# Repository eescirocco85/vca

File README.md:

# vca
Voltage Controlled Amp with loudness for our Record Player

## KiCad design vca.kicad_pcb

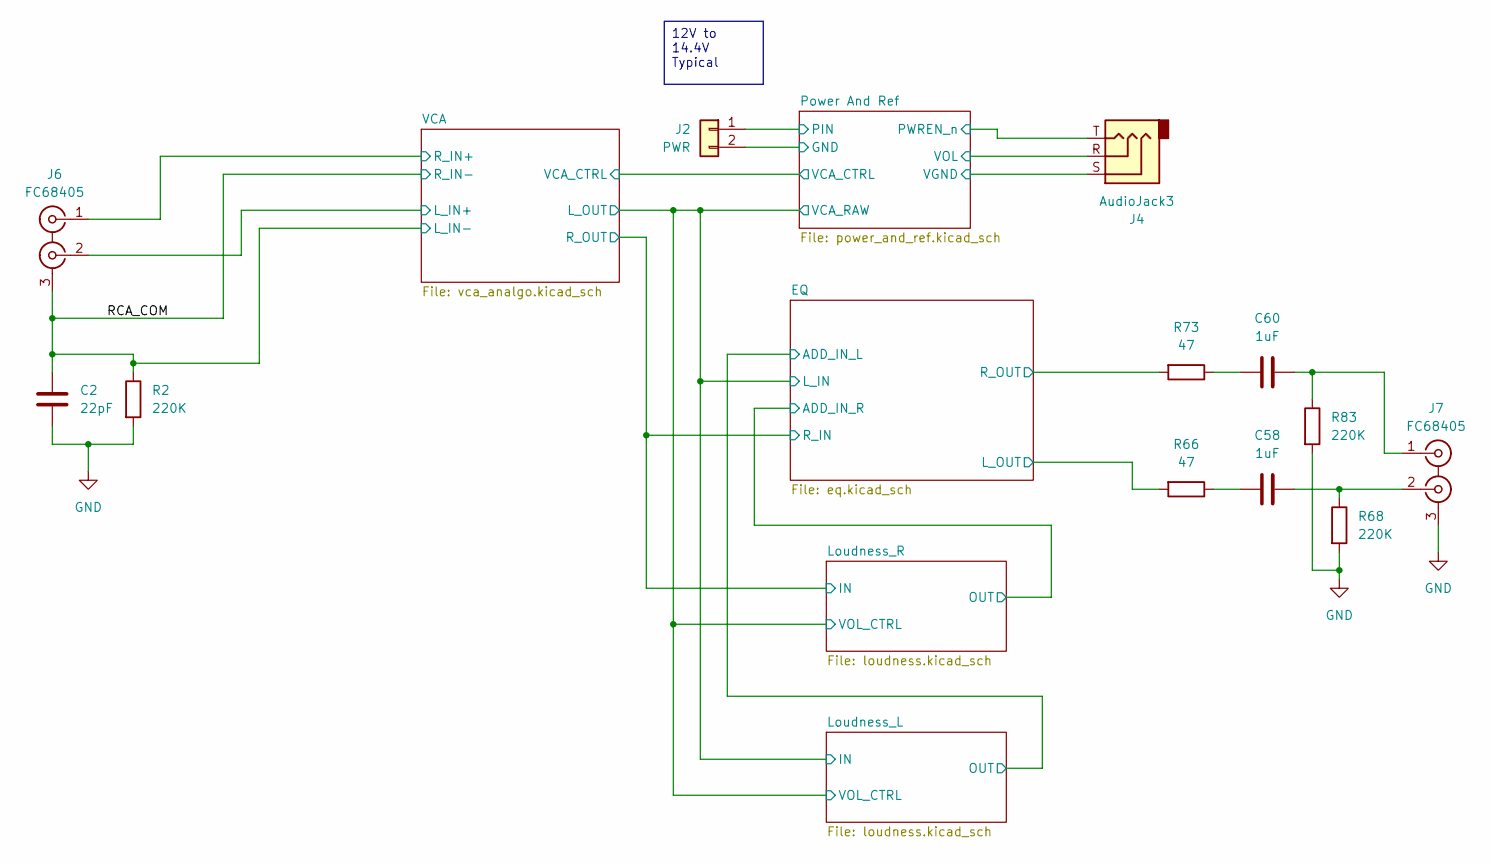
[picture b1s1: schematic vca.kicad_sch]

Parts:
C2: 22pF; C_0805_2012Metric_Pad1.18x1.45mm_HandSolder
C58, C60: 1uF; C_1210_3225Metric_Pad1.33x2.70mm_HandSolder
J2: PWR; BarrelJack_CUI_PJ-063AH_Horizontal_CircularHoles
J4: AudioJack3; Jack_3.5mm_CUI_SJ1-3533NG_Horizontal_CircularHoles
J6, J7: FC68405; DualVertRca
R2, R68, R83: 220K; R_1206_3216Metric_Pad1.30x1.75mm_HandSolder
R66, R73: 47; R_1206_3216Metric_Pad1.30x1.75mm_HandSolder

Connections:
/EQ/L_OUT: R66.2; also elsewhere on the board
/EQ/R_OUT: R73.2; also elsewhere on the board
/Power And Ref/PIN: J2.1; also elsewhere on the board
/Power And Ref/PWREN_n: J4.T; also elsewhere on the board
/Power And Ref/VGND: J4.S; also elsewhere on the board
/Power And Ref/VOL: J4.R; also elsewhere on the board
/RCA_COM: C2.1, J6.3 (EXT), R2.1; also elsewhere on the board
/VCA/L_IN+: J6.2 (IN2); also elsewhere on the board
/VCA/R_IN+: J6.1 (IN1); also elsewhere on the board
GND: C2.2, J2.2, J7.3 (EXT), R2.2, R68.2, R83.2; also elsewhere on the board
unnamed: C58.1, R66.1
unnamed: C60.1, R73.1
unnamed: C60.2, J7.1 (IN1), R83.1
unnamed: C58.2, J7.2 (IN2), R68.1

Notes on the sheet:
12V to 14.4V Typical

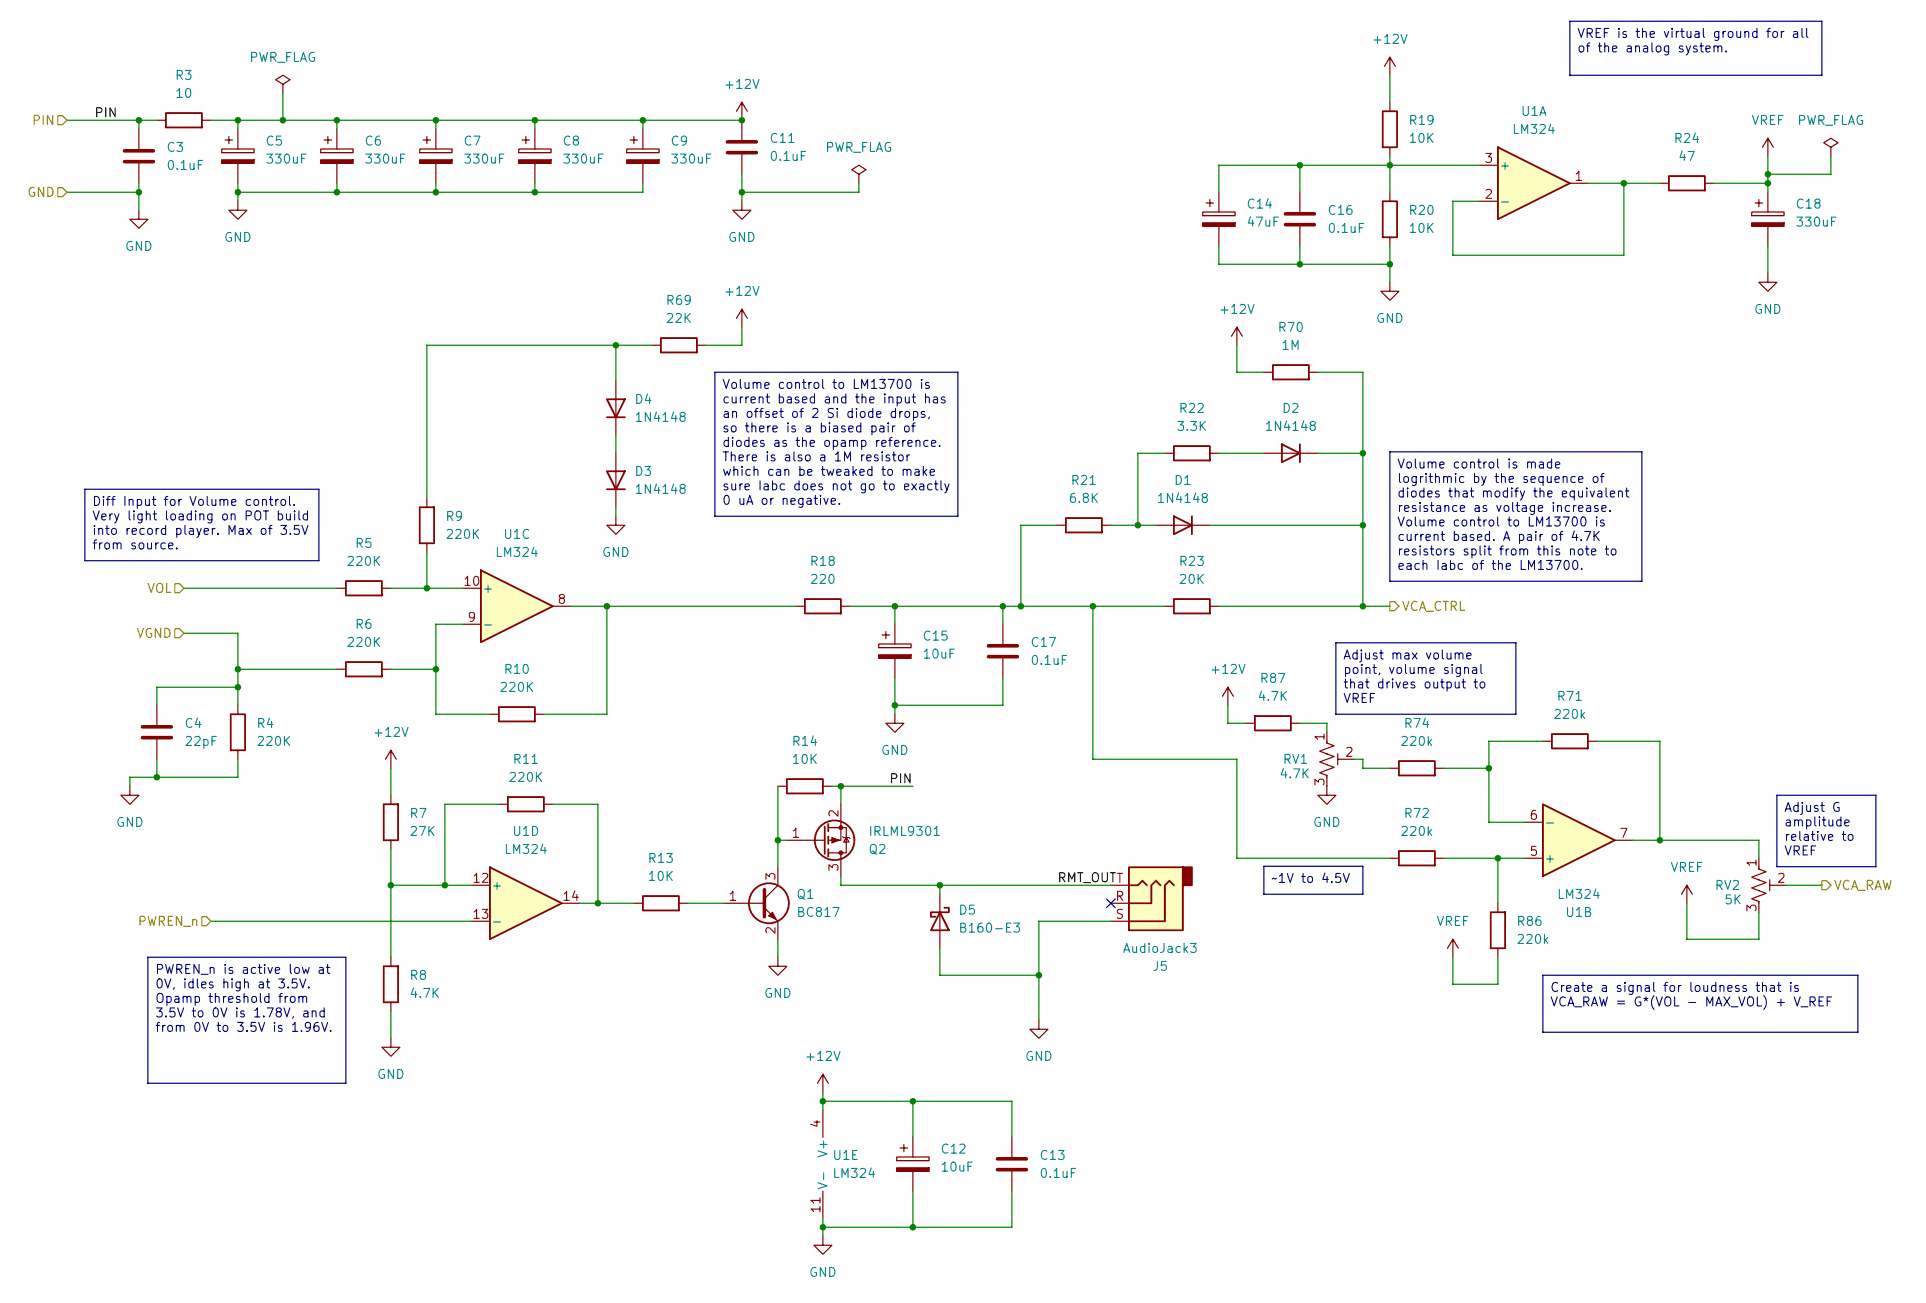
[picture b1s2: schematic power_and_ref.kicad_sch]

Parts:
C3, C11, C13, C16, C17: 0.1uF; C_0805_2012Metric_Pad1.18x1.45mm_HandSolder
C4: 22pF; C_0805_2012Metric_Pad1.18x1.45mm_HandSolder
C5, C6, C7, C8, C9, C18: 330uF; C_Radial_D10.0mm_H20.0mm_P5.00mm
C12, C15: 10uF; C_Radial_D5.0mm_H11.0mm_P2.00mm
C14: 47uF; C_Radial_D5.0mm_H11.0mm_P2.00mm
D1, D2, D3, D4: 1N4148; D_DO-35_SOD27_P7.62mm_Horizontal
D5: B160-E3; D_SMA
J5: AudioJack3; Jack_3.5mm_CUI_SJ1-3533NG_Horizontal_CircularHoles
Q1: BC817; SOT-23
Q2: IRLML9301; SOT-23
R3: 10; R_1206_3216Metric_Pad1.30x1.75mm_HandSolder
R4, R5, R6, R9, R10, R11: 220K; R_1206_3216Metric_Pad1.30x1.75mm_HandSolder
R7: 27K; R_1206_3216Metric_Pad1.30x1.75mm_HandSolder
R8, R87: 4.7K; R_1206_3216Metric_Pad1.30x1.75mm_HandSolder
R13, R14, R19, R20: 10K; R_1206_3216Metric_Pad1.30x1.75mm_HandSolder
R18: 220; R_1206_3216Metric_Pad1.30x1.75mm_HandSolder
R21: 6.8K; R_1206_3216Metric_Pad1.30x1.75mm_HandSolder
R22: 3.3K; R_1206_3216Metric_Pad1.30x1.75mm_HandSolder
R23: 20K; R_1206_3216Metric_Pad1.30x1.75mm_HandSolder
R24: 47; R_1206_3216Metric_Pad1.30x1.75mm_HandSolder
R69: 22K; R_1206_3216Metric_Pad1.30x1.75mm_HandSolder
R70: 1M; R_1206_3216Metric_Pad1.30x1.75mm_HandSolder
R71, R72, R74, R86: 220k; R_1206_3216Metric_Pad1.30x1.75mm_HandSolder
RV1: 4.7K
RV2: 5K
U1: LM324; SOIC-14_3.9x8.7mm_P1.27mm

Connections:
+12V: C5.1, C6.1, C7.1, C8.1, C9.1, C11.1, C12.1, C13.1, R3.2, R7.2, R19.1, R69.2, R70.1, R87.2, U1.4 (V+); also elsewhere on the board
/Power And Ref/PIN: C3.1, Q2.2 (S), R3.1, R14.2; also elsewhere on the board
/Power And Ref/PWREN_n: U1.13 (-); also elsewhere on the board
/Power And Ref/RMT_OUT: D5.1 (K), J5.T, Q2.3 (D)
/Power And Ref/VCA_CTRL: D1.1 (K), D2.1 (K), R23.2, R70.2; also elsewhere on the board
/Power And Ref/VGND: C4.1, R4.1, R6.1; also elsewhere on the board
/Power And Ref/VOL: R5.1; also elsewhere on the board
GND: C3.2, C4.2, C5.2, C6.2, C7.2, C8.2, C9.2, C11.2, C12.2, C13.2, C14.2, C15.2, C16.2, C17.2, C18.2, D3.1 (K), D5.2 (A), J5.S, Q1.2 (E), R4.2, R8.1, R20.2, RV1.3, U1.11 (V-); also elsewhere on the board
unnamed: C15.1, C17.1, R18.2, R21.1, R23.1, R72.1
unnamed: D1.2 (A), R21.2, R22.1
unnamed: D2.2 (A), R22.2
unnamed: D3.2 (A), D4.1 (K)
unnamed: D4.2 (A), R9.2, R69.1
unnamed: Q1.1 (B), R13.2
unnamed: Q1.3 (C), Q2.1 (G), R14.1
unnamed: R10.2, R18.1, U1.8
unnamed: R11.1, R13.1, U1.14
unnamed: R71.2, RV2.1, U1.7
unnamed: R74.1, RV1.2
unnamed: R87.1, RV1.1
unnamed: C14.1, C16.1, R19.2, R20.1, U1.3 (+)
unnamed: R24.1, U1.1, U1.2 (-)
unnamed: R72.2, R86.2, U1.5 (+)
unnamed: R71.1, R74.2, U1.6 (-)
unnamed: R5.2, R9.1, U1.10 (+)
unnamed: R6.2, R10.1, U1.9 (-)
unnamed: R7.1, R8.2, R11.2, U1.12 (+)
VREF: C18.1, R24.2, R86.1, RV2.3; also elsewhere on the board

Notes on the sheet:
~1V to 4.5V
PWREN_n is active low at 0V, idles high at 3.5V. Opamp threshold from 3.5V to 0V is 1.78V, and from 0V to 3.5V is 1.96V.
Diff Input for Volume control. Very light loading on POT build into record player. Max of 3.5V from source.
Volume control is made logrithmic by the sequence of diodes that modify the equivalent resistance as voltage increase. Volume control to LM13700 is current based. A pair of 4.7K resistors split from this note to each Iabc of the LM13700.
Volume control to LM13700 is current based and the input has an offset of 2 Si diode drops, so there is a biased pair of diodes as the opamp reference. There is also a 1M resistor which can be tweaked to make sure Iabc does not go to exactly 0 uA or negative.
Adjust max volume point, volume signal that drives output to VREF
Adjust G amplitude relative to VREF
VREF is the virtual ground for all of the analog system.
Create a signal for loudness that is VCA_RAW = G*(VOL - MAX_VOL) + V_REF

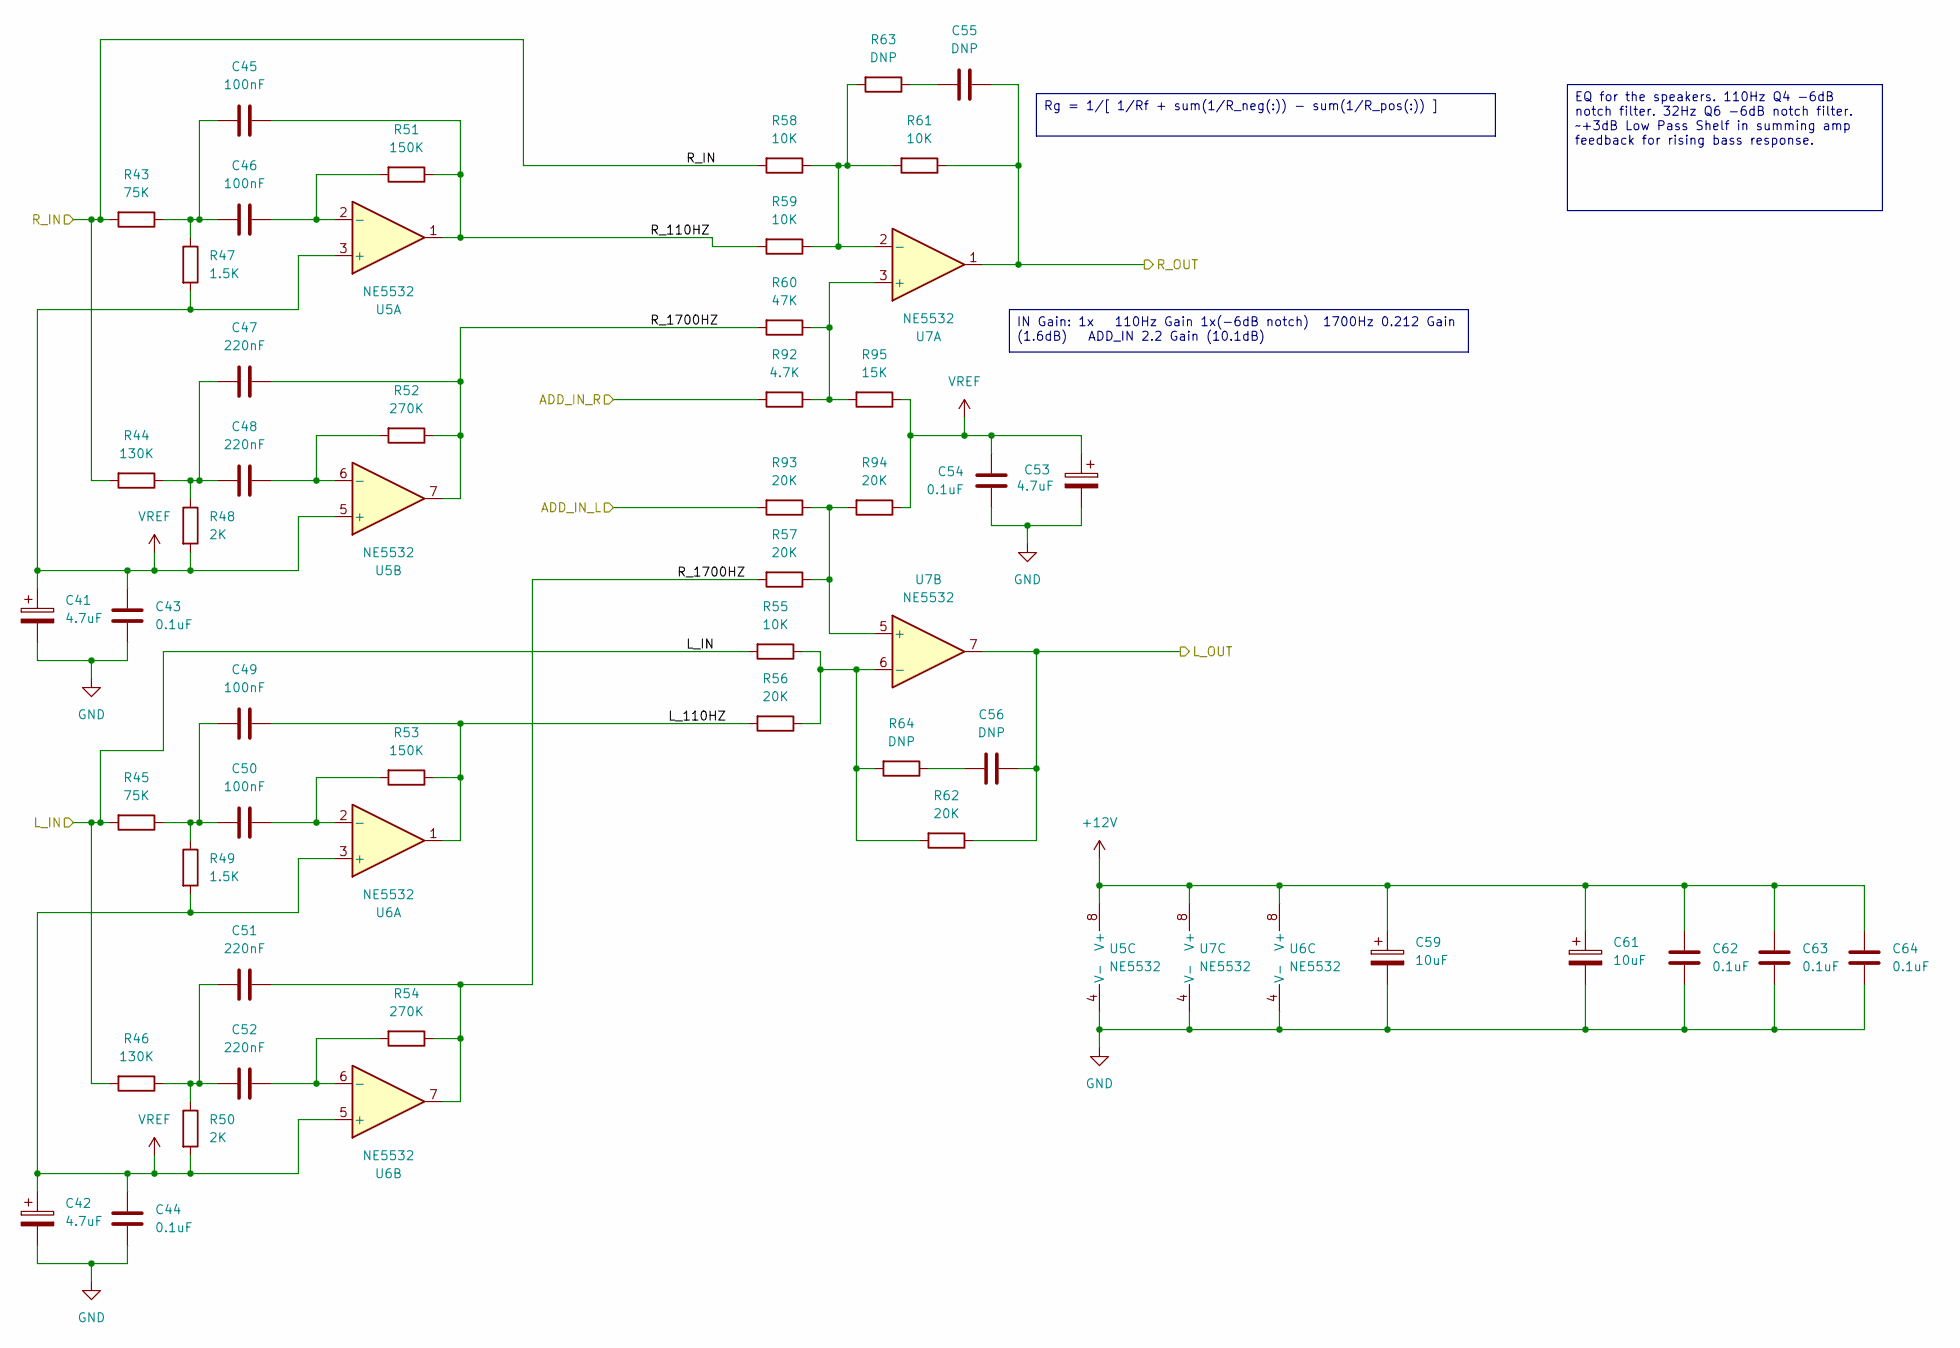
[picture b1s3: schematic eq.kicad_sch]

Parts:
C41, C42, C53: 4.7uF; C_Radial_D5.0mm_H7.0mm_P2.00mm
C43, C44, C54, C62, C63, C64: 0.1uF; C_0805_2012Metric_Pad1.18x1.45mm_HandSolder
C45, C46, C49, C50: 100nF; C_1812_4532Metric_Pad1.57x3.40mm_HandSolder
C47, C48, C51, C52: 220nF; C_2220_5750Metric_Pad1.97x5.40mm_HandSolder
C55, C56: DNP; C_1812_4532Metric_Pad1.57x3.40mm_HandSolder
C59, C61: 10uF; C_Radial_D5.0mm_H11.0mm_P2.00mm
R43, R45: 75K; R_1206_3216Metric_Pad1.30x1.75mm_HandSolder
R44, R46: 130K; R_1206_3216Metric_Pad1.30x1.75mm_HandSolder
R47, R49: 1.5K; R_1206_3216Metric_Pad1.30x1.75mm_HandSolder
R48, R50: 2K; R_1206_3216Metric_Pad1.30x1.75mm_HandSolder
R51, R53: 150K; R_1206_3216Metric_Pad1.30x1.75mm_HandSolder
R52, R54: 270K; R_1206_3216Metric_Pad1.30x1.75mm_HandSolder
R55, R58, R59, R61: 10K; R_1206_3216Metric_Pad1.30x1.75mm_HandSolder
R56, R57, R62, R93, R94: 20K; R_1206_3216Metric_Pad1.30x1.75mm_HandSolder
R60: 47K; R_1206_3216Metric_Pad1.30x1.75mm_HandSolder
R63, R64: DNP; R_1206_3216Metric_Pad1.30x1.75mm_HandSolder
R92: 4.7K; R_1206_3216Metric_Pad1.30x1.75mm_HandSolder
R95: 15K; R_1206_3216Metric_Pad1.30x1.75mm_HandSolder
U5, U6, U7: NE5532; SOIC-8_3.9x4.9mm_P1.27mm

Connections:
+12V: C59.1, C61.1, C62.1, C63.1, C64.1, U5.8 (V+), U6.8 (V+), U7.8 (V+); also elsewhere on the board
/EQ/ADD_IN_L: R93.2; also elsewhere on the board
/EQ/ADD_IN_R: R92.2; also elsewhere on the board
/EQ/L_110HZ: C49.2, R53.1, R56.2, U6.1
/EQ/L_IN: R45.2, R46.2, R55.2; also elsewhere on the board
/EQ/L_OUT: C56.2, R62.1, U7.7; also elsewhere on the board
/EQ/R_110HZ: C45.2, R51.1, R59.2, U5.1
/EQ/R_1700HZ: C47.2, C51.2, R52.1, R54.1, R57.2, R60.2, U5.7, U6.7
/EQ/R_IN: R43.2, R44.2, R58.2; also elsewhere on the board
/EQ/R_OUT: C55.2, R61.1, U7.1; also elsewhere on the board
GND: C41.2, C42.2, C43.2, C44.2, C53.2, C54.2, C59.2, C61.2, C62.2, C63.2, C64.2, U5.4 (V-), U6.4 (V-), U7.4 (V-); also elsewhere on the board
unnamed: C45.1, C46.1, R43.1, R47.1
unnamed: C47.1, C48.1, R44.1, R48.1
unnamed: C49.1, C50.1, R45.1, R49.1
unnamed: C51.1, C52.1, R46.1, R50.1
unnamed: C55.1, R63.1
unnamed: C56.1, R64.1
unnamed: C46.2, R51.2, U5.2 (-)
unnamed: C48.2, R52.2, U5.6 (-)
unnamed: C50.2, R53.2, U6.2 (-)
unnamed: C52.2, R54.2, U6.6 (-)
unnamed: R60.1, R92.1, R95.2, U7.3 (+)
unnamed: R58.1, R59.1, R61.2, R63.2, U7.2 (-)
unnamed: R57.1, R93.1, R94.2, U7.5 (+)
unnamed: R55.1, R56.1, R62.2, R64.2, U7.6 (-)
VREF: C41.1, C42.1, C43.1, C44.1, C53.1, C54.1, R47.2, R48.2, R49.2, R50.2, R94.1, R95.1, U5.3 (+), U5.5 (+), U6.3 (+), U6.5 (+); also elsewhere on the board

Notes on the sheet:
EQ for the speakers. 110Hz Q4 -6dB notch filter. 32Hz Q6 -6dB notch filter. ~+3dB Low Pass Shelf in summing amp feedback for rising bass response.
Rg = 1/[ 1/Rf + sum(1/R_neg(:)) - sum(1/R_pos(:)) ]
IN Gain: 1x 110Hz Gain 1x(-6dB notch) 1700Hz 0.212 Gain (1.6dB) ADD_IN 2.2 Gain (10.1dB)

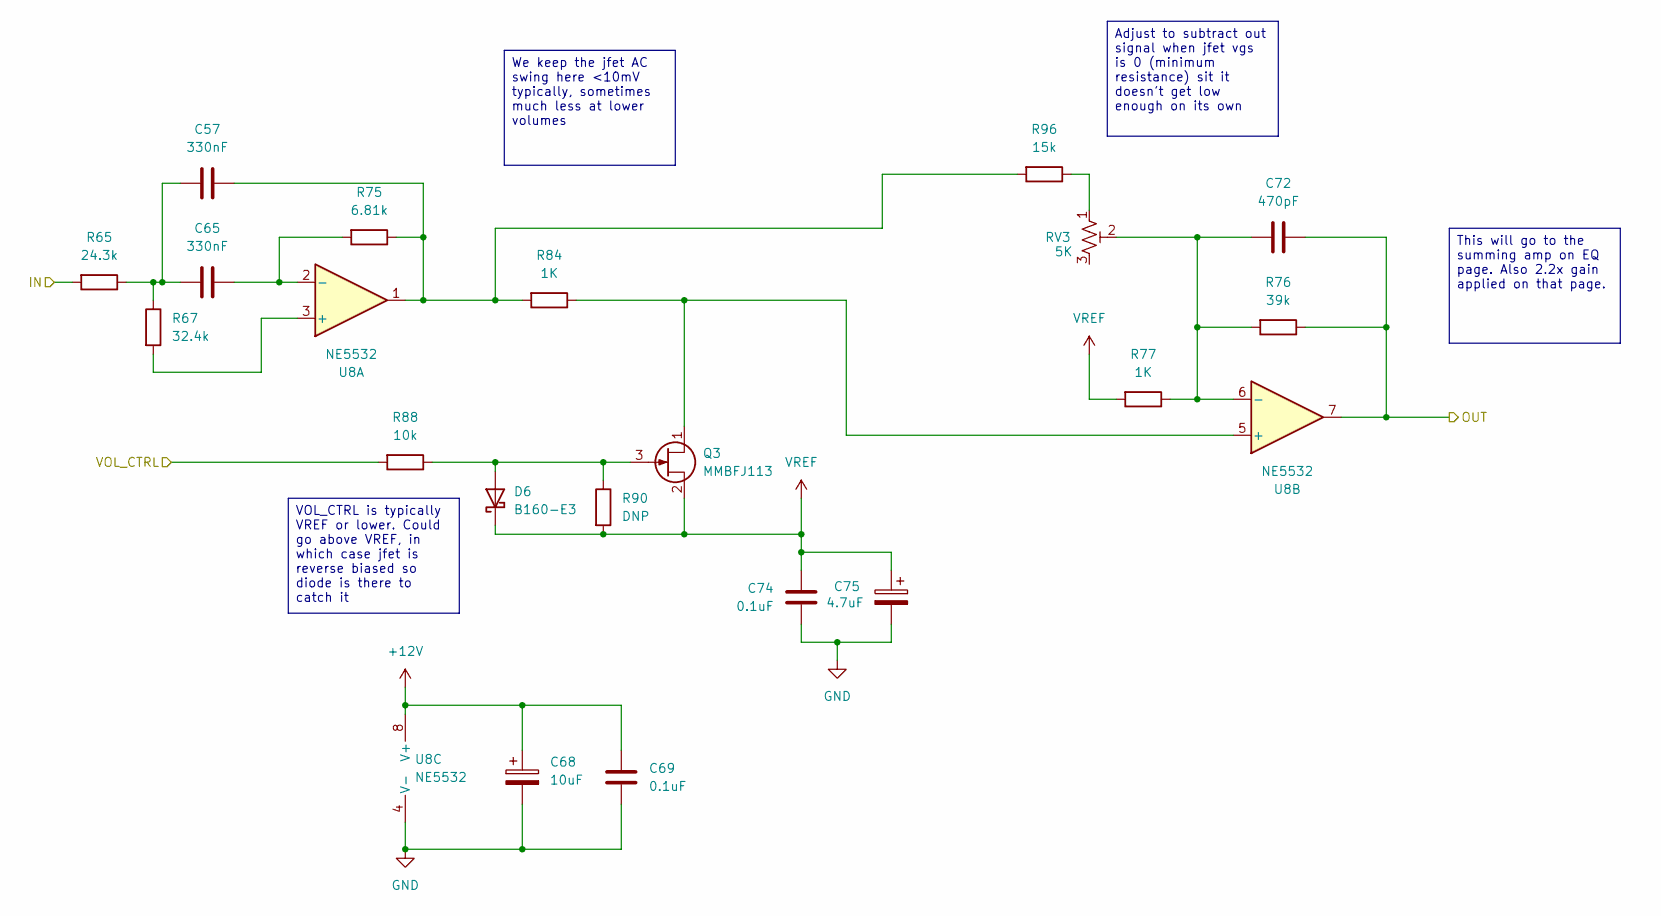
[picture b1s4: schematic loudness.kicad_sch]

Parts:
C57, C65: 330nF; C_2220_5750Metric_Pad1.97x5.40mm_HandSolder
C68: 10uF; C_Radial_D5.0mm_H11.0mm_P2.00mm
C69, C74: 0.1uF; C_0805_2012Metric_Pad1.18x1.45mm_HandSolder
C72: 470pF; C_0805_2012Metric_Pad1.18x1.45mm_HandSolder
C75: 4.7uF; C_Radial_D5.0mm_H7.0mm_P2.00mm
D6: B160-E3; D_SMA
Q3: MMBFJ113; SOT-23
R65: 24.3k; R_1206_3216Metric_Pad1.30x1.75mm_HandSolder
R67: 32.4k; R_1206_3216Metric_Pad1.30x1.75mm_HandSolder
R75: 6.81k; R_1206_3216Metric_Pad1.30x1.75mm_HandSolder
R76: 39k; R_1206_3216Metric_Pad1.30x1.75mm_HandSolder
R77, R84: 1K; R_1206_3216Metric_Pad1.30x1.75mm_HandSolder
R88: 10k; R_1206_3216Metric_Pad1.30x1.75mm_HandSolder
R90: DNP; R_1206_3216Metric_Pad1.30x1.75mm_HandSolder
R96: 15k; R_1206_3216Metric_Pad1.30x1.75mm_HandSolder
RV3: 5K
U8: NE5532

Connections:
+12V: C68.1, C69.1, U8.8 (V+); also elsewhere on the board
/EQ/ADD_IN_R: C72.2, R76.1; also elsewhere on the board
/EQ/L_IN: R88.2; also elsewhere on the board
/EQ/R_IN: R65.2; also elsewhere on the board
GND: C68.2, C69.2, C74.2, C75.2, U8.4 (V-); also elsewhere on the board
unnamed: C57.1, C65.1, R65.1, R67.1
unnamed: C57.2, R75.1, R84.2
unnamed: D6.2 (A), Q3.3 (G), R88.1, R90.1
unnamed: Q3.1 (D), R84.1
unnamed: R96.1, RV3.1
unnamed: C65.2, R75.2
unnamed: C72.1, R76.2, R77.1
VREF: C74.1, C75.1, D6.1 (K), Q3.2 (S), R77.2, R90.2; also elsewhere on the board

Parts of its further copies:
C70: 10uF; C_Radial_D5.0mm_H11.0mm_P2.00mm
C71, C76: 0.1uF; C_0805_2012Metric_Pad1.18x1.45mm_HandSolder
C73: 470pF; C_0805_2012Metric_Pad1.18x1.45mm_HandSolder
C77: 4.7uF; C_Radial_D5.0mm_H7.0mm_P2.00mm
D7: B160-E3; D_SMA
Q4: MMBFJ113; SOT-23
R81, R85: 1K; R_1206_3216Metric_Pad1.30x1.75mm_HandSolder
R89: 10k; R_1206_3216Metric_Pad1.30x1.75mm_HandSolder
R91: DNP; R_1206_3216Metric_Pad1.30x1.75mm_HandSolder

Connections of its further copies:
+12V: C70.1, C71.1; also elsewhere on the board
/EQ/ADD_IN_L: C73.2; also elsewhere on the board
/EQ/L_IN: R89.2; also elsewhere on the board
GND: C70.2, C71.2, C76.2, C77.2; also elsewhere on the board
unnamed 38: R85.2; also elsewhere on the board
unnamed: D7.2 (A), Q4.3 (G), R89.1, R91.1
unnamed: Q4.1 (D), R85.1
unnamed 87: C73.1, R81.1; also elsewhere on the board
VREF: C76.1, C77.1, D7.1 (K), Q4.2 (S), R81.2, R91.2; also elsewhere on the board

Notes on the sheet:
We keep the jfet AC swing here <10mV typically, sometimes much less at lower volumes
Adjust to subtract out signal when jfet vgs is 0 (minimum resistance) sit it doesn't get low enough on its own
This will go to the summing amp on EQ page. Also 2.2x gain applied on that page.
VOL_CTRL is typically VREF or lower. Could go above VREF, in which case jfet is reverse biased so diode is there to catch it

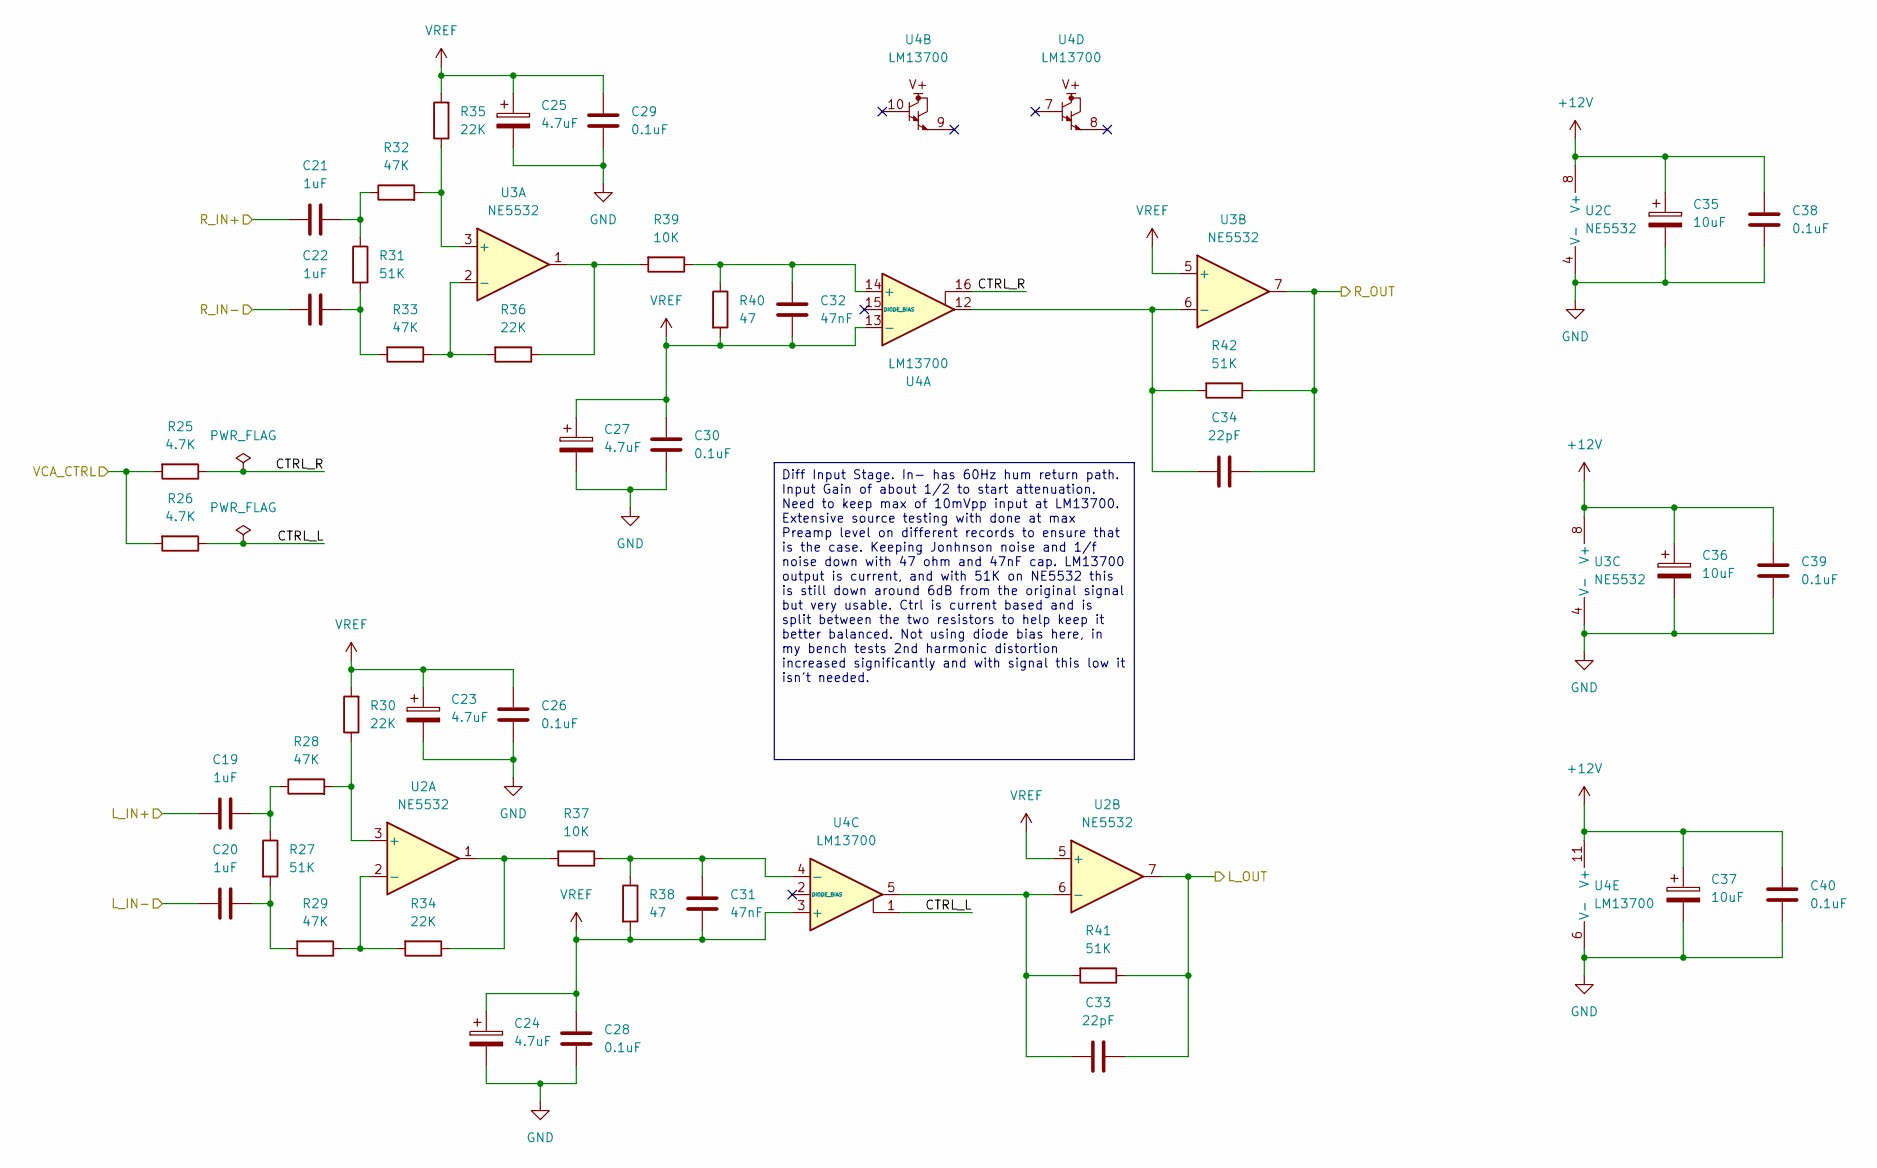
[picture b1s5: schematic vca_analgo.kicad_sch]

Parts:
C19, C20, C21, C22: 1uF; C_1210_3225Metric_Pad1.33x2.70mm_HandSolder
C23, C24, C25, C27: 4.7uF; C_Radial_D5.0mm_H7.0mm_P2.00mm
C26, C28, C29, C30, C38, C39, C40: 0.1uF; C_0805_2012Metric_Pad1.18x1.45mm_HandSolder
C31, C32: 47nF; C_1812_4532Metric_Pad1.57x3.40mm_HandSolder
C33, C34: 22pF; C_0805_2012Metric_Pad1.18x1.45mm_HandSolder
C35, C36, C37: 10uF; C_Radial_D5.0mm_H11.0mm_P2.00mm
R25, R26: 4.7K; R_1206_3216Metric_Pad1.30x1.75mm_HandSolder
R27, R31, R41, R42: 51K; R_1206_3216Metric_Pad1.30x1.75mm_HandSolder
R28, R29, R32, R33: 47K; R_1206_3216Metric_Pad1.30x1.75mm_HandSolder
R30, R34, R35, R36: 22K; R_1206_3216Metric_Pad1.30x1.75mm_HandSolder
R37, R39: 10K; R_1206_3216Metric_Pad1.30x1.75mm_HandSolder
R38, R40: 47; R_1206_3216Metric_Pad1.30x1.75mm_HandSolder
U2, U3: NE5532; SOIC-8_3.9x4.9mm_P1.27mm
U4: LM13700; SOIC-16_3.9x9.9mm_P1.27mm

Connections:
+12V: C35.1, C36.1, C37.1, C38.1, C39.1, C40.1, U2.8 (V+), U3.8 (V+), U4.11 (V+); also elsewhere on the board
/EQ/L_IN: C33.2, R41.1, U2.7; also elsewhere on the board
/EQ/R_IN: C34.2, R42.1, U3.7; also elsewhere on the board
/Power And Ref/VCA_CTRL: R25.2, R26.2; also elsewhere on the board
/RCA_COM: C20.1, C22.1; also elsewhere on the board
/VCA/CTRL_L: R26.1, U4.1
/VCA/CTRL_R: R25.1, U4.16
/VCA/L_IN+: C19.1; also elsewhere on the board
/VCA/R_IN+: C21.1; also elsewhere on the board
GND: C23.2, C24.2, C25.2, C26.2, C27.2, C28.2, C29.2, C30.2, C35.2, C36.2, C37.2, C38.2, C39.2, C40.2, U2.4 (V-), U3.4 (V-), U4.6 (V-); also elsewhere on the board
unnamed: C19.2, R27.1, R28.1
unnamed: C20.2, R27.2, R29.2
unnamed: C21.2, R31.1, R32.1
unnamed: C22.2, R31.2, R33.2
unnamed: R34.1, R37.2, U2.1
unnamed: R36.1, R39.2, U3.1
unnamed: R28.2, R30.1, U2.3 (+)
unnamed: R29.1, R34.2, U2.2 (-)
unnamed: C33.1, R41.2, U2.6 (-), U4.5
unnamed: R32.2, R35.1, U3.3 (+)
unnamed: R33.1, R36.2, U3.2 (-)
unnamed: C34.1, R42.2, U3.6 (-), U4.12
unnamed: C32.2, R39.1, R40.1, U4.14 (+)
unnamed: C31.2, R37.1, R38.1, U4.4 (-)
VREF: C23.1, C24.1, C25.1, C26.1, C27.1, C28.1, C29.1, C30.1, C31.1, C32.1, R30.2, R35.2, R38.2, R40.2, U2.5 (+), U3.5 (+), U4.3 (+), U4.13 (-); also elsewhere on the board

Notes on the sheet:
Diff Input Stage. In- has 60Hz hum return path. Input Gain of about 1/2 to start attenuation. Need to keep max of 10mVpp input at LM13700. Extensive source testing with done at max Preamp level on different records to ensure that is the case. Keeping Jonhnson noise and 1/f noise down with 47 ohm an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

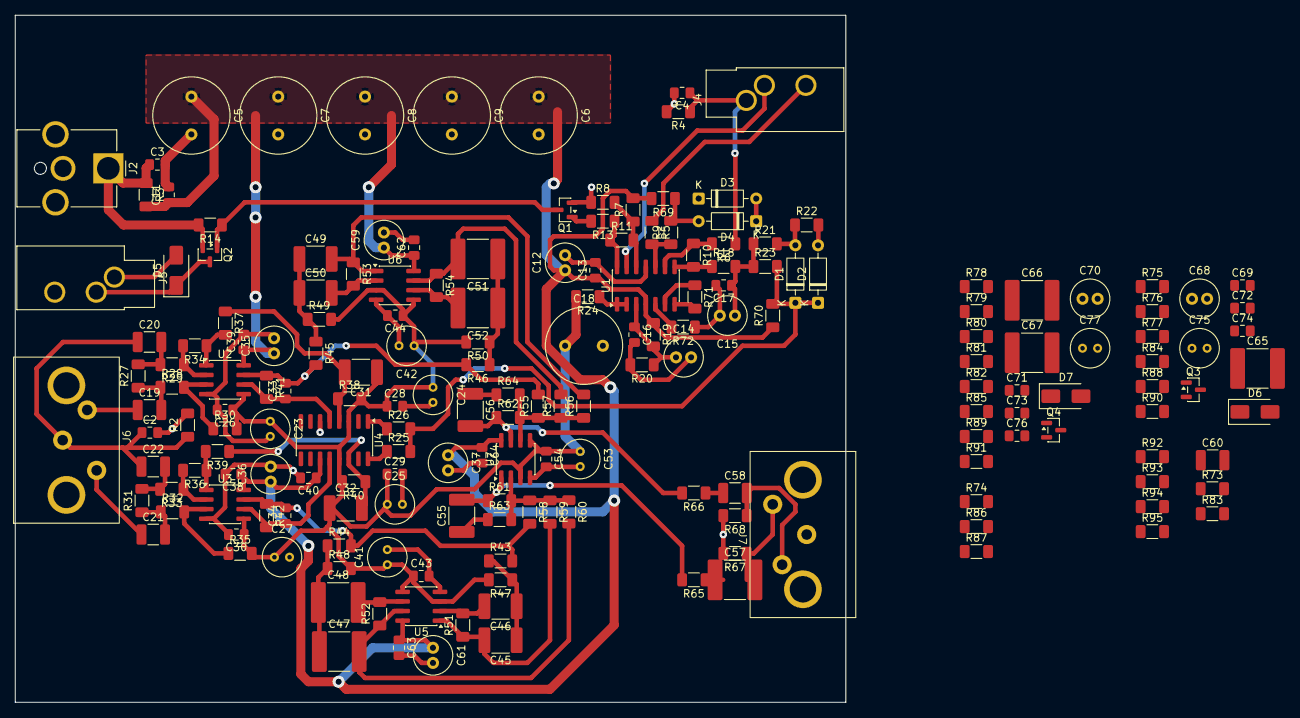
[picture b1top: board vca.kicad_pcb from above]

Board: 2 copper layers, 110.0 x 91.0 mm, 188 parts (0 on the bottom side), 84 nets.

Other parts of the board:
C66, C67: 220nF; C_2220_5750Metric_Pad1.97x5.40mm_HandSolder
R78: 75K; R_1206_3216Metric_Pad1.30x1.75mm_HandSolder
R79: 1.5K; R_1206_3216Metric_Pad1.30x1.75mm_HandSolder
R80: 150K; R_1206_3216Metric_Pad1.30x1.75mm_HandSolder
R82: 47K; R_1206_3216Metric_Pad1.30x1.75mm_HandSolder

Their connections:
/EQ/ADD_IN_L: R82.1; also elsewhere on the board
/EQ/L_IN: R78.2; also elsewhere on the board
unnamed: C66.1, C67.1, R78.1, R79.1
unnamed 38: C66.2, R80.1; also elsewhere on the board
unnamed: C67.2, R80.2
unnamed 87: R82.2; also elsewhere on the board
